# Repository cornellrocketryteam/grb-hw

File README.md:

# GPS Radio Beacon

This repository contains the hardware design for the GPS Radio Beacon.

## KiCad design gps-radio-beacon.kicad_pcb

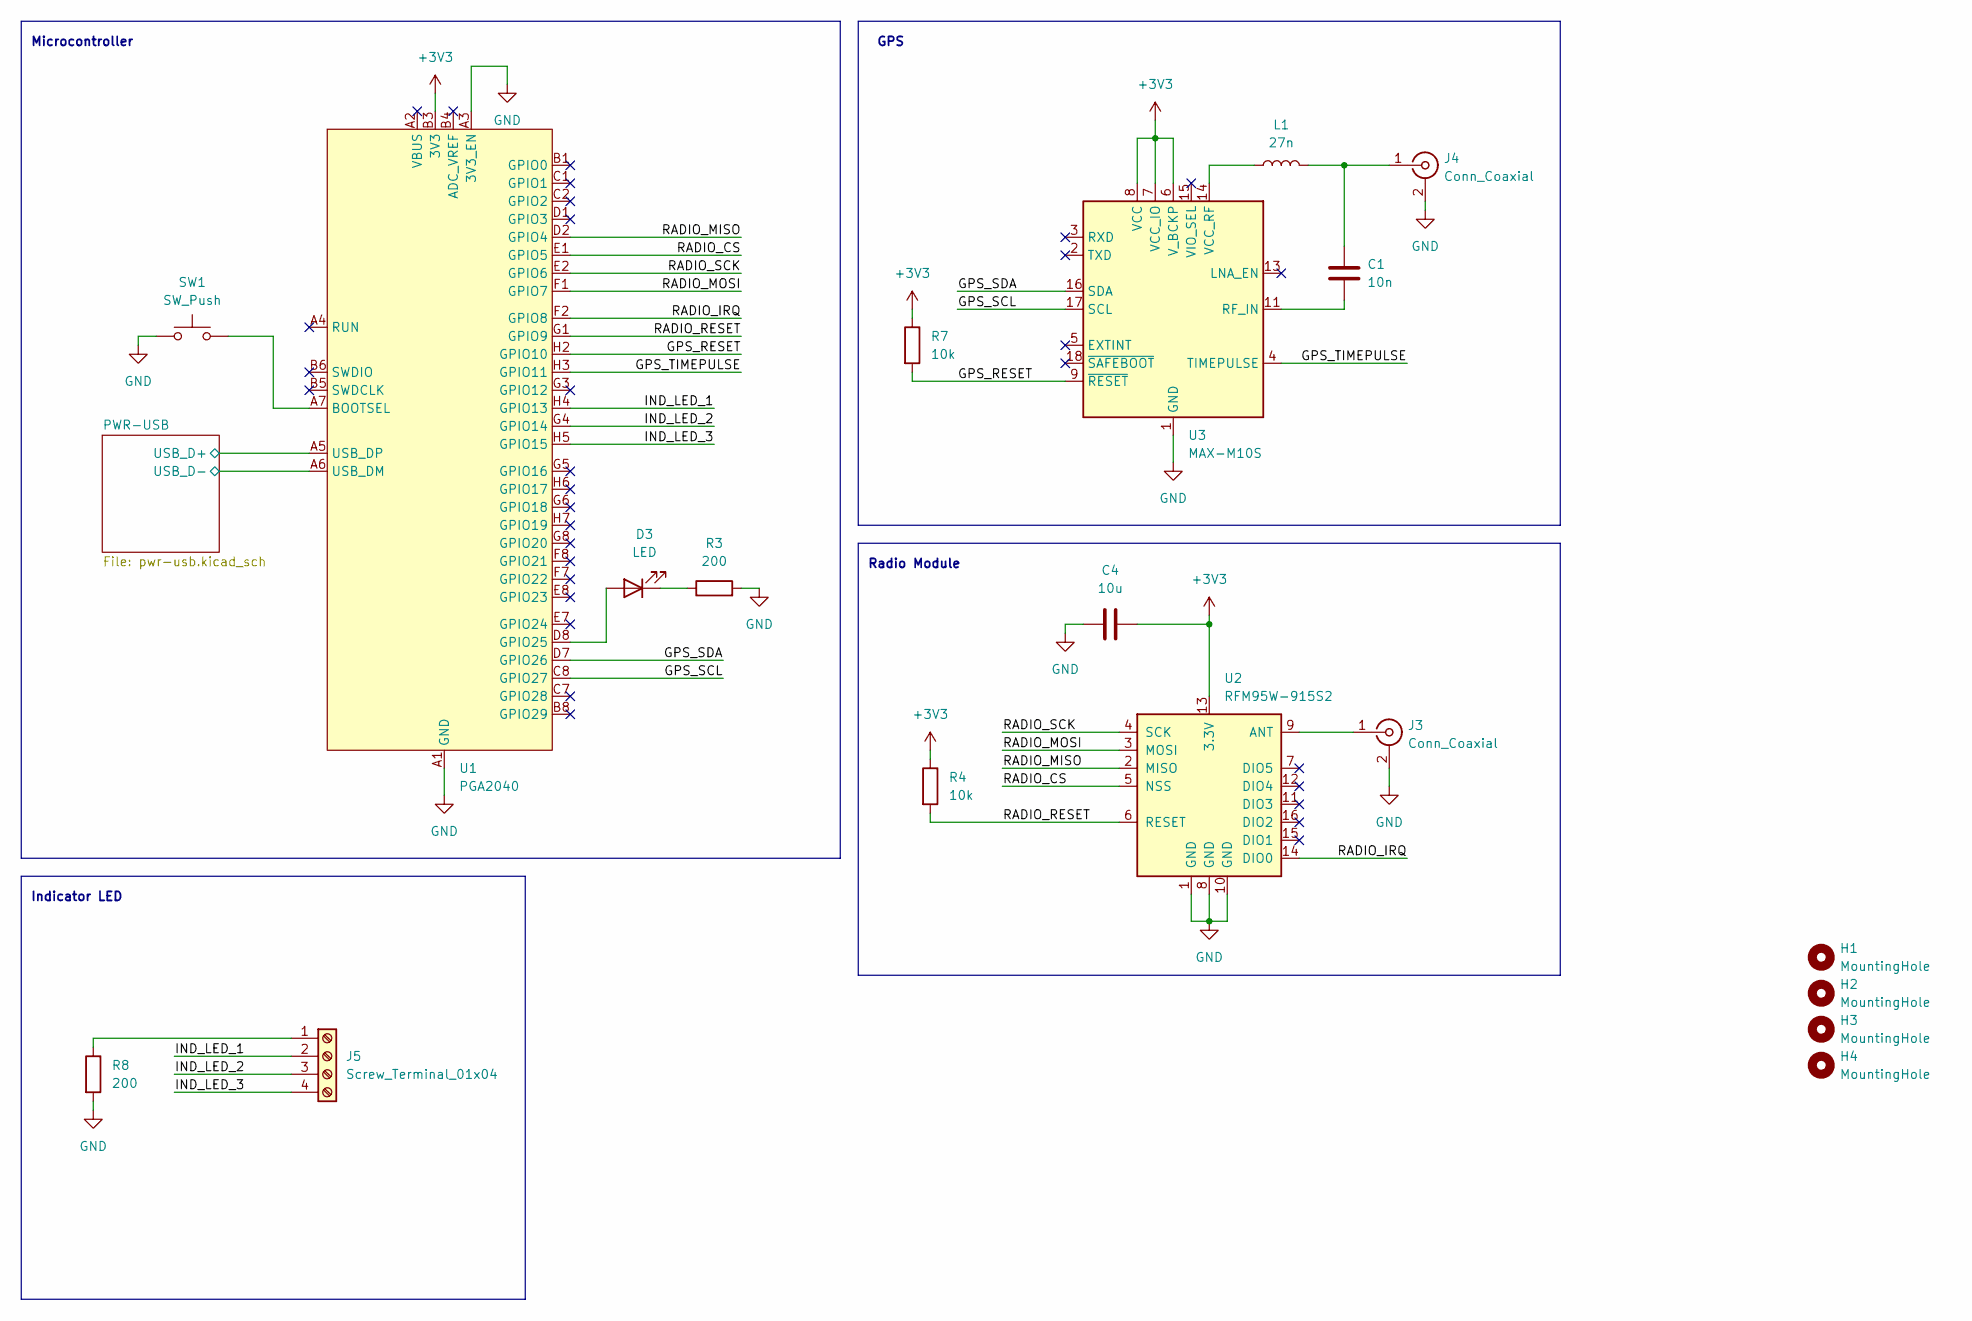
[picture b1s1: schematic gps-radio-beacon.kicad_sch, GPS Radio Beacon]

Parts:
C1: 10n; C_1206_3216Metric_Pad1.33x1.80mm_HandSolder
C4: 10u; C_1206_3216Metric_Pad1.33x1.80mm_HandSolder
D3: LED; LED_D3.0mm
H1, H2, H3, H4: MountingHole; MountingHole_3.2mm_M3
J3, J4: Conn_Coaxial; SMA_Molex_73251-1153_EdgeMount_Horizontal
J5: Screw_Terminal_01x04; TerminalBlock_Phoenix_MKDS-1,5-4-5.08_1x04_P5.08mm_Horizont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
L1: 27n; L_1210_3225Metric_Pad1.42x2.65mm_HandSolder
R3, R8: 200; R_0805_2012Metric_Pad1.20x1.40mm_HandSolder
R4, R7: 10k; R_0805_2012Metric_Pad1.20x1.40mm_HandSolder
SW1: SW_Push; SW_PUSH_6mm
U1: PGA2040
U2: RFM95W-915S2; HOPERF_RFM9XW_SMD
U3: MAX-M10S; ublox_MAX

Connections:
+3V3: C4.2, R4.1, R7.1, U1.B3 (3V3), U2.13 (3.3V), U3.6 (V_BCKP), U3.7 (VCC_IO), U3.8 (VCC); also elsewhere on the board
/GPS_RESET: R7.2, U1.H2 (GPIO10), U3.9 (~RESET)
/GPS_SCL: U1.C8 (GPIO27), U3.17 (SCL)
/GPS_SDA: U1.D7 (GPIO26), U3.16 (SDA)
/GPS_TIMEPULSE: U1.H3 (GPIO11), U3.4 (TIMEPULSE)
/IND_LED_1: J5.2, U1.H4 (GPIO13)
/IND_LED_2: J5.3, U1.G4 (GPIO14)
/IND_LED_3: J5.4, U1.H5 (GPIO15)
/PWR-USB/USB_D+: U1.A5 (USB_DP); also elsewhere on the board
/PWR-USB/USB_D-: U1.A6 (USB_DM); also elsewhere on the board
/RADIO_CS: U1.E1 (GPIO5), U2.5 (NSS)
/RADIO_IRQ: U1.F2 (GPIO8), U2.14 (DIO0)
/RADIO_MISO: U1.D2 (GPIO4), U2.2 (MISO)
/RADIO_MOSI: U1.F1 (GPIO7), U2.3 (MOSI)
/RADIO_RESET: R4.2, U1.G1 (GPIO9), U2.6 (RESET)
/RADIO_SCK: U1.E2 (GPIO6), U2.4 (SCK)
<NO NET>: C4.1, J3.2 (Ext), J4.2 (Ext), R3.2, R8.2, SW1.1, U1.A1 (GND), U1.A3 (3V3_EN), U1.A8, U1.B2, U1.B7, U1.G2, U1.G7, U1.H1, U1.H8, U2.1 (GND), U2.8 (GND), U2.10 (GND), U3.1 (GND), U3.10 (GND), U3.12 (GND); also elsewhere on the board
unnamed: C1.1, J4.1 (In), L1.2
unnamed: C1.2, U3.11 (RF_IN)
unnamed: D3.1 (K), R3.1
unnamed: D3.2 (A), U1.D8 (GPIO25)
unnamed: J3.1 (In), U2.9 (ANT)
unnamed: J5.1, R8.1
unnamed: L1.1, U3.14 (VCC_RF)
unnamed: SW1.2, U1.A7 (BOOTSEL)

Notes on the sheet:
Indicator LED
Radio Module
Microcontroller
GPS

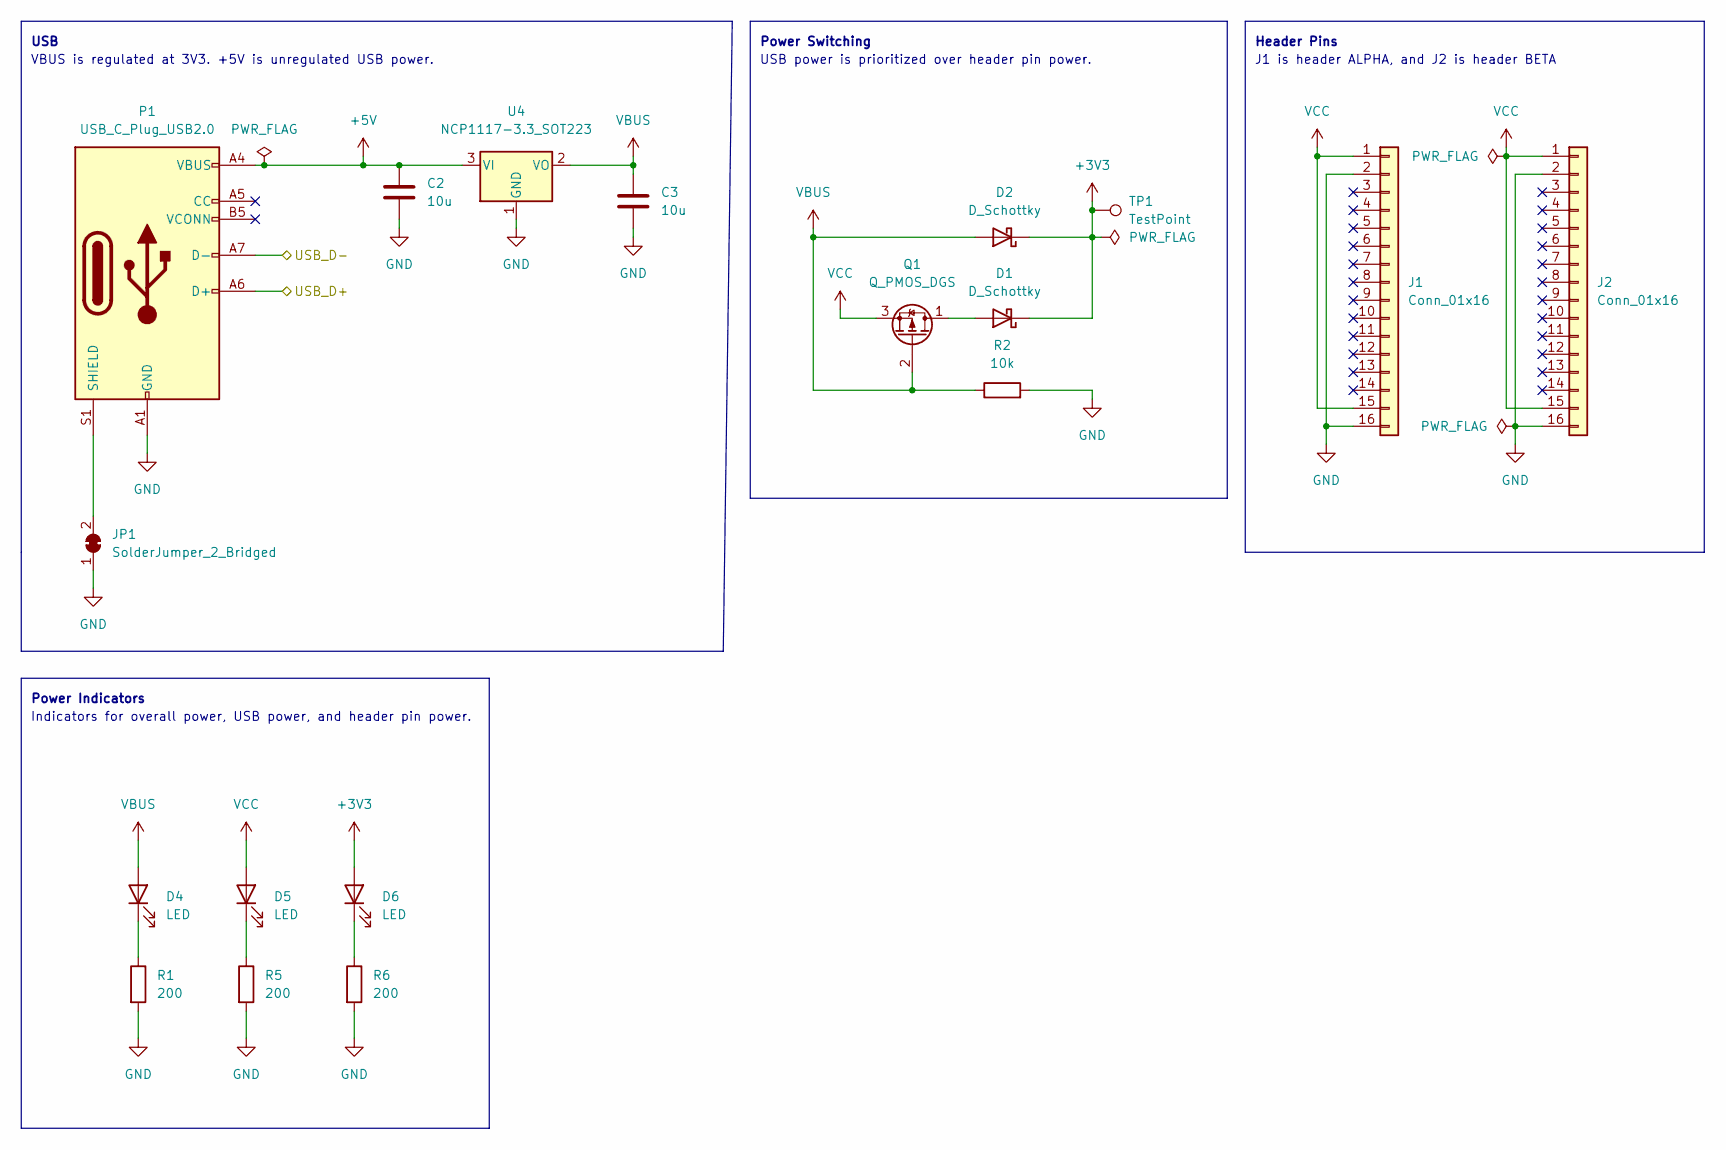
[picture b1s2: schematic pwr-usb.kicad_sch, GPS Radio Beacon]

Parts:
C2, C3: 10u; C_1206_3216Metric_Pad1.33x1.80mm_HandSolder
D1, D2: D_Schottky; D_SOD-323_HandSoldering
D4, D5, D6: LED; LED_D3.0mm
J1, J2: Conn_01x16; PinHeader_1x16_P2.54mm_Vertical
JP1: SolderJumper_2_Bridged; SolderJumper-2_P1.3mm_Bridged_RoundedPad1.0x1.5mm
P1: USB_C_Plug_USB2.0; USB_C_Receptacle_GCT_USB4085
Q1: Q_PMOS_DGS; SC-59_Handsoldering
R1, R5, R6: 200; R_0805_2012Metric_Pad1.20x1.40mm_HandSolder
R2: 10k; R_0805_2012Metric_Pad1.20x1.40mm_HandSolder
TP1: TestPoint; TestPoint_Loop_D2.54mm_Drill1.5mm_Beaded
U4: NCP1117-3.3_SOT223; SOT-223-3_TabPin2

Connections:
+3V3: D1.1 (K), D2.1 (K), D6.2 (A), TP1.1; also elsewhere on the board
+5V: C2.1, P1.A4 (VBUS), P1.A9 (VBUS), P1.B4 (VBUS), P1.B9 (VBUS), U4.3 (VI)
/PWR-USB/USB_D+: P1.A6 (D+); also elsewhere on the board
/PWR-USB/USB_D-: P1.A7 (D-); also elsewhere on the board
<NO NET>: C2.2, C3.2, J1.2, J1.16, J2.2, J2.16, JP1.1 (A), P1.A1 (GND), P1.A12 (GND), P1.B1 (GND), P1.B12 (GND), R1.2, R2.2, R5.2, R6.2, U4.1 (GND); also elsewhere on the board
unnamed: D1.2 (A), Q1.1 (D)
unnamed: D4.1 (K), R1.1
unnamed: D5.1 (K), R5.1
unnamed: D6.1 (K), R6.1
unnamed: JP1.2 (B), P1.S1 (SHIELD)
VBUS: C3.1, D2.2 (A), D4.2 (A), Q1.2 (G), R2.1, U4.2 (VO)
VCC: D5.2 (A), J1.1, J1.15, J2.1, J2.15, Q1.3 (S)

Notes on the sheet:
Power Switching
USB
USB power is prioritized over header pin power.
Power Indicators
VBUS is regulated at 3V3. +5V is unregulated USB power.
Indicators for overall power, USB power, and header pin power.
J1 is header ALPHA, and J2 is header BETA
Header Pins

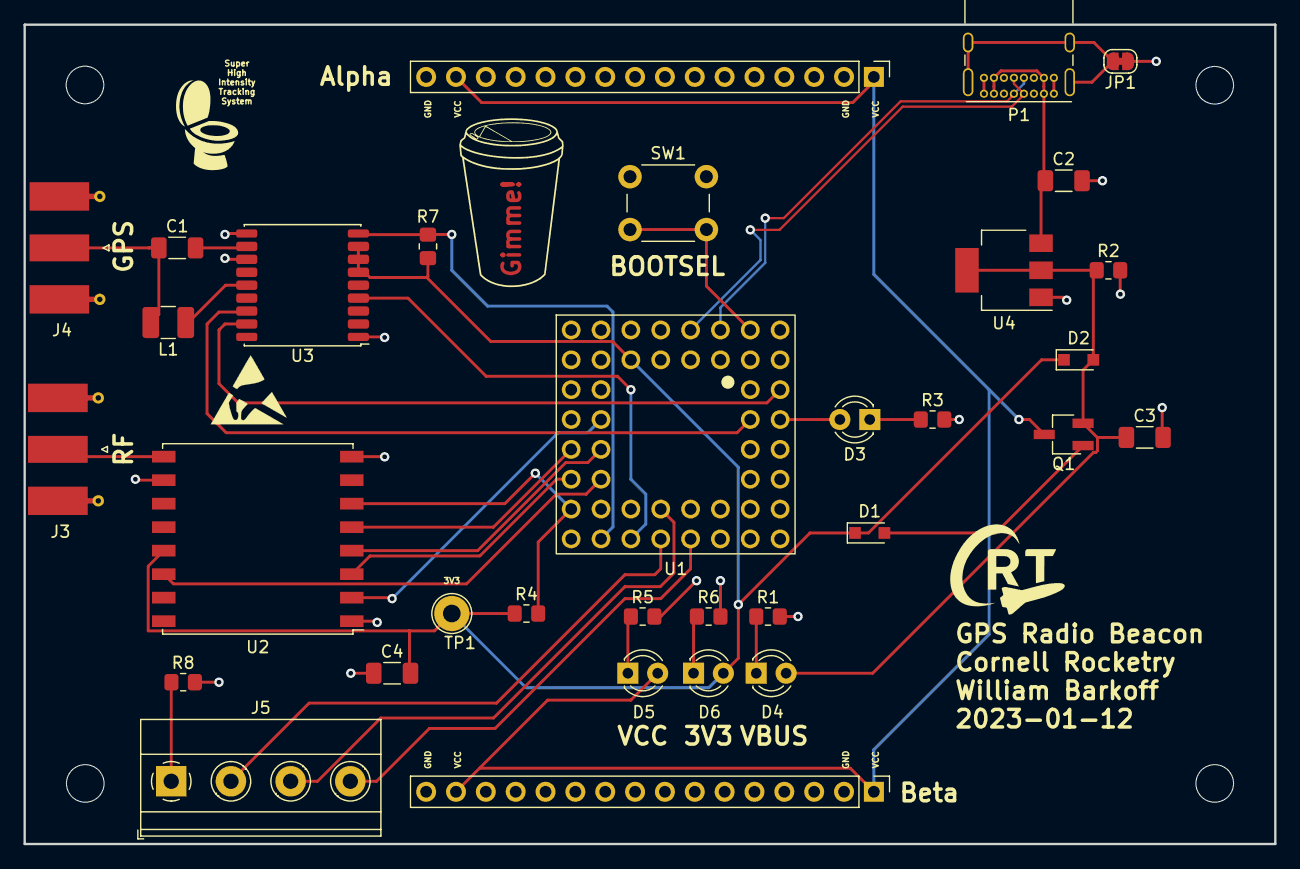
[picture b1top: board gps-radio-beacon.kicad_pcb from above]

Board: 2 copper layers, 106.4 x 69.7 mm, 37 parts (0 on the bottom side), 33 nets.

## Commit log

2022-10-24 commit current codebase
2022-10-24 fix ERC violations
2022-10-24 Add README
2022-10-24 factor out power and USB to another schematic
2022-10-24 remove extraneous symbol library
2022-10-24 refactoring, fix typos
2022-10-24 migrate GPS to M10S
2022-10-25 fix missing libraries
2022-11-04 fix schematic issues
2022-11-04 begin assigning footprints
2022-11-18 update schematic
2022-11-23 redesign pim
2022-11-24 redesign for use with RFM95
2022-11-24 bendy traces
2022-11-24 update bom
2022-11-24 update silkscreen
2022-11-28 Revert "update silkscreen"
    This reverts commit 1eaeaa331c0a90a38e124b6b08bc37b13ba27824.
2022-11-28 Revert "update bom"
    This reverts commit 52b414b356ff6ae39cc421828713dbb64186a9da.
2022-11-28 rearrange a few components
2022-11-28 Revert "bendy traces"
    This reverts commit 8a4ff923ad6d744258f9f7e3ddda1145dac49418.
2022-11-29 reroute some stuff
2022-11-29 Add license
2022-11-30 final updates!
2022-12-01 update site theme
2022-12-01 fix tpyo
2023-01-12 Add BOOTSEL button
2023-04-10 Fix many bugs with the initial version
2023-04-28 Final changes for comp

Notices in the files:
gps-radio-beacon.kicad_pcb:
Licensed under CERN-OHL-W v2
